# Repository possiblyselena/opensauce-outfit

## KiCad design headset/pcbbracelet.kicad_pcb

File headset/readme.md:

# Mecha-inspired Headset Attachments (and a bracelet accerlerometer)

I took inspiration from [Nasha's wing headset!](https://vt.tiktok.com/ZSCBQKjPd/) Since at undercity me and my buddies made a gundam outfit, I wanted to make a outfit for Opensauce. Plus demoing will be really easy because I'll just be wearing it.

## CAD
I designed the headset attachment and the electronics case through Onshape. I made the case look like a walkman, to be a bit more performative.

## PCB
For the accelerometer, I wanted to make it with lace, so I made a small-ish pcb with holes on the side to tie the lace and I'll make a pocket with the lace to fit the battery.

## BOM

Things I already have:
ESP32, MPU6050 (essentially the same as sen142), breadboard, wires, basic assembly things
| Item Name             | Price (CAD) | Quantity | Total (CAD) | Purchase Link | 
|-----------------------|-------------|----------|-------------|----------------|
| 2pc SG90 Servo Motor | 9.99$ | 1 | 9.99$ | [Amazon](https://www.amazon.ca/Servo-Helicopter-Airplane-Remote-Control/dp/B09L525KDT/ref=sr_1_5?crid=34HWQBXT8V32I&dib=eyJ2IjoiMSJ9.lB4sKn152VCulFDSWZREaQKsBY1f47T5zTrOWkggWz6o29wHPzpGaezLYTDF5j9YDjOF2-Be6fnQFoniWeTVeog5F76RXJoD1975FQQU7kRHofisq_CoLa8HxtHKcpEMv6ZJApCI24m0toXThBvgovdDTaCEhHExNfqfFOA1z7cYHUjcEAJ1X12H72CjFBWkh0u2evTOo0TemK6UIR4qCvGx5ZuB5BZPjpTtXmuetclEnJaIYVnKs8l14_iS83vYa8z5hT7lU7AaESKIAyDGOc2MM-MLoNI8L-aA8_RBbug.OnCujQ50fPdUj5sg2o5UQIn_tEcg-Uc0c3T1IRc_tp4&dib_tag=se&keywords=2pc+servos&qid=1782616651&sprefix=2pc+servos%2Caps%2C119&sr=8-5) |
| ESP32 C3 Devkit | 21.99$ | 1 | 21.99$ | [Amazon](https://www.amazon.ca/ESP32-C3-Blue-Tooth-Internet-Development-ESP32-C3-DevKitM-1/dp/B0DQJ8KGJM/ref=sr_1_1_sspa?crid=20OITKQMD4UNK&dib=eyJ2IjoiMSJ9.xL2w3IwP7v_dTK_eSsR-XJVw2KZWvNploiQXYmuV3wjMtZFhEESDoFnjQxTxqKTS0XveGVrDAm_S7jKpQKXenOuKuIXC8JvlcIdq85tL_Q6j421w4zlQcCYyjumDkyHGEozdGuAx2UVCeOyXk-knJagE6XwDMz_HUnxtAyGZyss9b3HYjB1_CPP5FDwFjMvka78aHBCWglh_-AiKDvjNhEgqBoUyvB5HJsYhfeHqmNYp0WmFQ_n3BY_gSgvJ2iH8cqhMTHFp_Z9X6I0MiPTGSE2jCit6wqZXc6YDQHeXDIs.TSmrqjff2Nopq9ZYE9S6yyi6kHHkAekmwD6LJR2bqAA&dib_tag=se&keywords=esp+32+devkitc+c3&qid=1782617069&sprefix=esp+32+devkit+c3%2Caps%2C144&sr=8-1-spons&sp_csd=d2lkZ2V0TmFtZT1zcF9hdGY&psc=1) |
| 2pc Lipo Battery | 21.99$ | 1 | 21.99$ | [Amazon](https://www.amazon.ca/Rechargeable-Controller-CUH-ZCT1-Electronic-Bluetooth/dp/B0CG178SHB/ref=sr_1_5?crid=37V9S3HSW8FWH&dib=eyJ2IjoiMSJ9.Ig80C9FPZMDP6OZVlEMddYtKekPGsA6gflmkYTcaJLdS5S-S-7lMY-gVBui4mIA9Bb5xFRwe-ees-3FQPoEfJtlj7vVaGqONRlM_F_8ZE0MJiRiuZT3rIJUABpq9Xj8MOF5VcWCjjg6PhFnt57f8VE3YhPArscAdSLWPXSGCmvtXxwPlsuP9_gZLxA4EGniIk9YQT51bMaj_-adbg9yQRH6q_lQ0yeWq06xC8xVSdKLD3mB69YetcGo1A1J3tGmg3Gf0u43ABDZmsxYBdgkRPsODpjRi_10Mys3QCahDFgA.05bsjhzHxu-FM3ppHEQ-eFWVtnVoLrA0EBFctOQSVXs&dib_tag=se&keywords=lipo+battery&qid=1782616967&sprefix=lipo+batter%2Caps%2C171&sr=8-5)|
| Velcro | 7.23$ | 1 | 7.23$ | [Amazon](https://www.amazon.ca/EILKBLA-Strips-Adhesive-Fastener-Mounting/dp/B0DFCN752Q/ref=sr_1_7?crid=1GUVIIWOQ81ID&dib=eyJ2IjoiMSJ9.UaP0FlQC7kWk-MntfrZdMqDVk-MssZkwYtXJstO-MDm6F_nVnHCdCSRH6sFK_4XqQQX1KG-Npw1t9s3BpH2vpOJBjJIhpJYKuxZrmRYT8aEh9bDHoo9SIwB2FsCYJ610l5Ddr5jWArDv6rxRJoZcgRNEkKaVLKZ3rlJsoqIsNXg_b2SjM88JpiEzqwiEI7RCtvs52KQ2Uu2hwgYeZmioS34o0cauWq6VyNbDZLIVlPxIa6DmW_7_lED-nBBjKOM8TJzcvXaQypPMx1wQQUg8p9QKwC4qbW3c5-TCMb7bISU.4IAdjpTpywW73G5bgv8BcWg7qzbs9O4_Rs03qL-Fva0&dib_tag=se&keywords=velcro&qid=1782617265&sprefix=velcro%2Caps%2C144&sr=8-7) |
| PCB | 2.40$ | 1 | 2.40$ | JLCPCB |

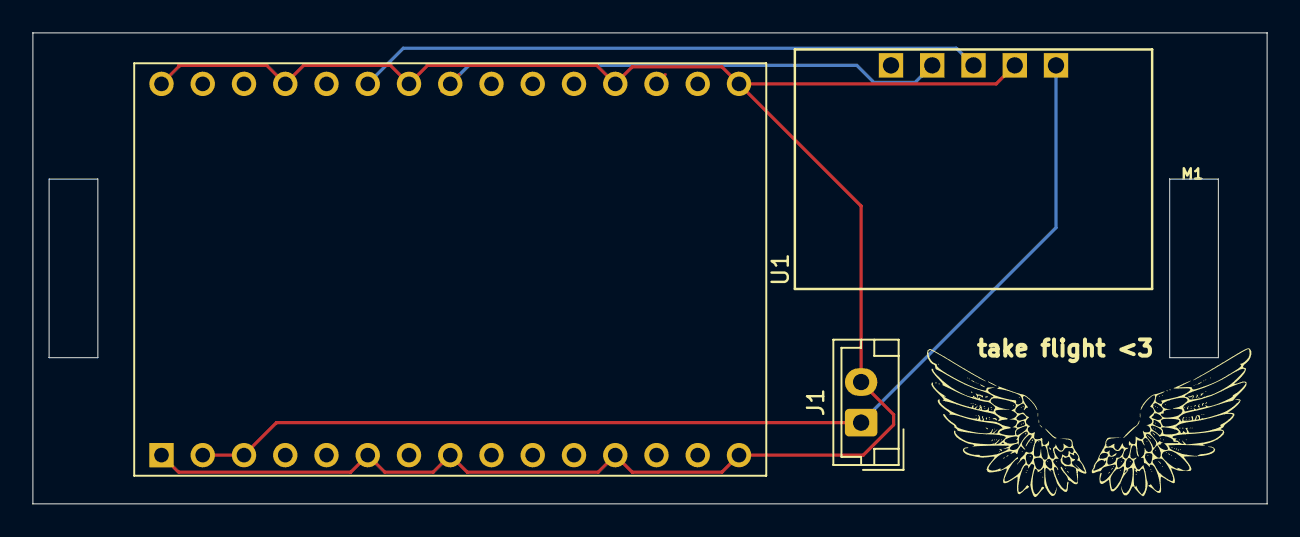
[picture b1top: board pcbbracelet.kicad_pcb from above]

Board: 2 copper layers, 76.0 x 29.0 mm, 3 parts (0 on the bottom side), 4 nets.

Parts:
J1: B2B-PH-K-S_LF__SN_; JST_EH_B2B-EH-A_1x02_P2.50mm_Vertical
M1: SEN0142
U1: ESP32-C3-DevKitM-1

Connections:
GND: J1.2, M1.2 (GND), U1.1 (GND), U1.6 (GND), U1.8 (GND), U1.12 (GND), U1.15 (GND), U1.16 (GND), U1.19 (GND), U1.24 (GND), U1.27 (GND), U1.30 (GND)
unnamed: J1.1, M1.1 (VIN), U1.2 (3V3), U1.3 (3V3)
SCL: M1.4 (SCL), U1.23 (IO7)
SDA: M1.3 (SDA), U1.25 (IO8)

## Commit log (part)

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2026-06-23 Rename headset/completedrightside.stl to headset/cad/completedrightside.stl
2026-06-23 add cad files
2026-06-23 add pcb files
2026-06-23 Rename headset/pcbbracelet.csv to headset/pcb/pcbbracelet.csv
2026-06-23 shove into pcb folder
2026-06-28 ai placeholder scripts
2026-06-28 put pcb files together
2026-06-28 unfinshed readme.md
2026-06-28 finished readme/md for now
